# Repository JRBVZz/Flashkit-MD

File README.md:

#### Flashkit MD дампер картриджей для Sega Mega Drive

Данный дампер/программатор позволяет читать и перезаписывать [совместимые картриджи](https://github.com/JRBVZz/SEGA-MD-Cart). Главное отличие данного форка - это возможность использовать адаптеры для флэш памяти в корпусах TSOP48, таким образом можно выпаять память из несовместимого картриджа и перезаписать её. При этом swap byte для записываемого ROM делать не нужно!

**Схема**  
[Schematic PDF](Flashkit-Pics/Flashkit-Schematic.pdf)

**Интерактивный BOM**  
[BoM](BOM/Flashkit-iBOM.html) (для корректного просмотра нужно скачать raw файл)

**Прошивка**  
В папке Flashkit-Firmware находятся исходники проекта для Quartus, логика не менялась, был изменен порядок выводов EPM240.

**Софт**  
В папке Flashkit-Soft находится программа для работы с Flashkit и её исходники. Продвинутую версию программы от MiGeRA можно [скачать здесь](https://github.com/MiGeRA/FlashKit-MD-Plus).

**Использование адаптеров**  
В продаже можно найти дешевые TSOP56 адаптеры под пайку (A) и TSOP48 адаптер для TL866 (B), нужна только верхняя часть с кроваткой для микросхемы. Учтите, что у дампера для разных адаптеров свое посадочное место. Для того, чтобы программа увидела адаптер с установленной памятью, необходимо соединить перемычку "FLASH" на плате дампера.

При запайке чипа памяти в адаптер TSOP56, выводы микросхемы должны располагаться посередине посадочной площадки, т.е. сверху и снизу должно быть свободно по 2 контактные площадки.

Спасибо [**Krikzz**](https://github.com/krikzz) за этот отличный дампер.  
Проект создан в [**KiCad 9**](https://www.kicad.org/).  
PS Герберы не выкладываю специально - это мой небольшой вклад в популяризацию KiCad :smile:

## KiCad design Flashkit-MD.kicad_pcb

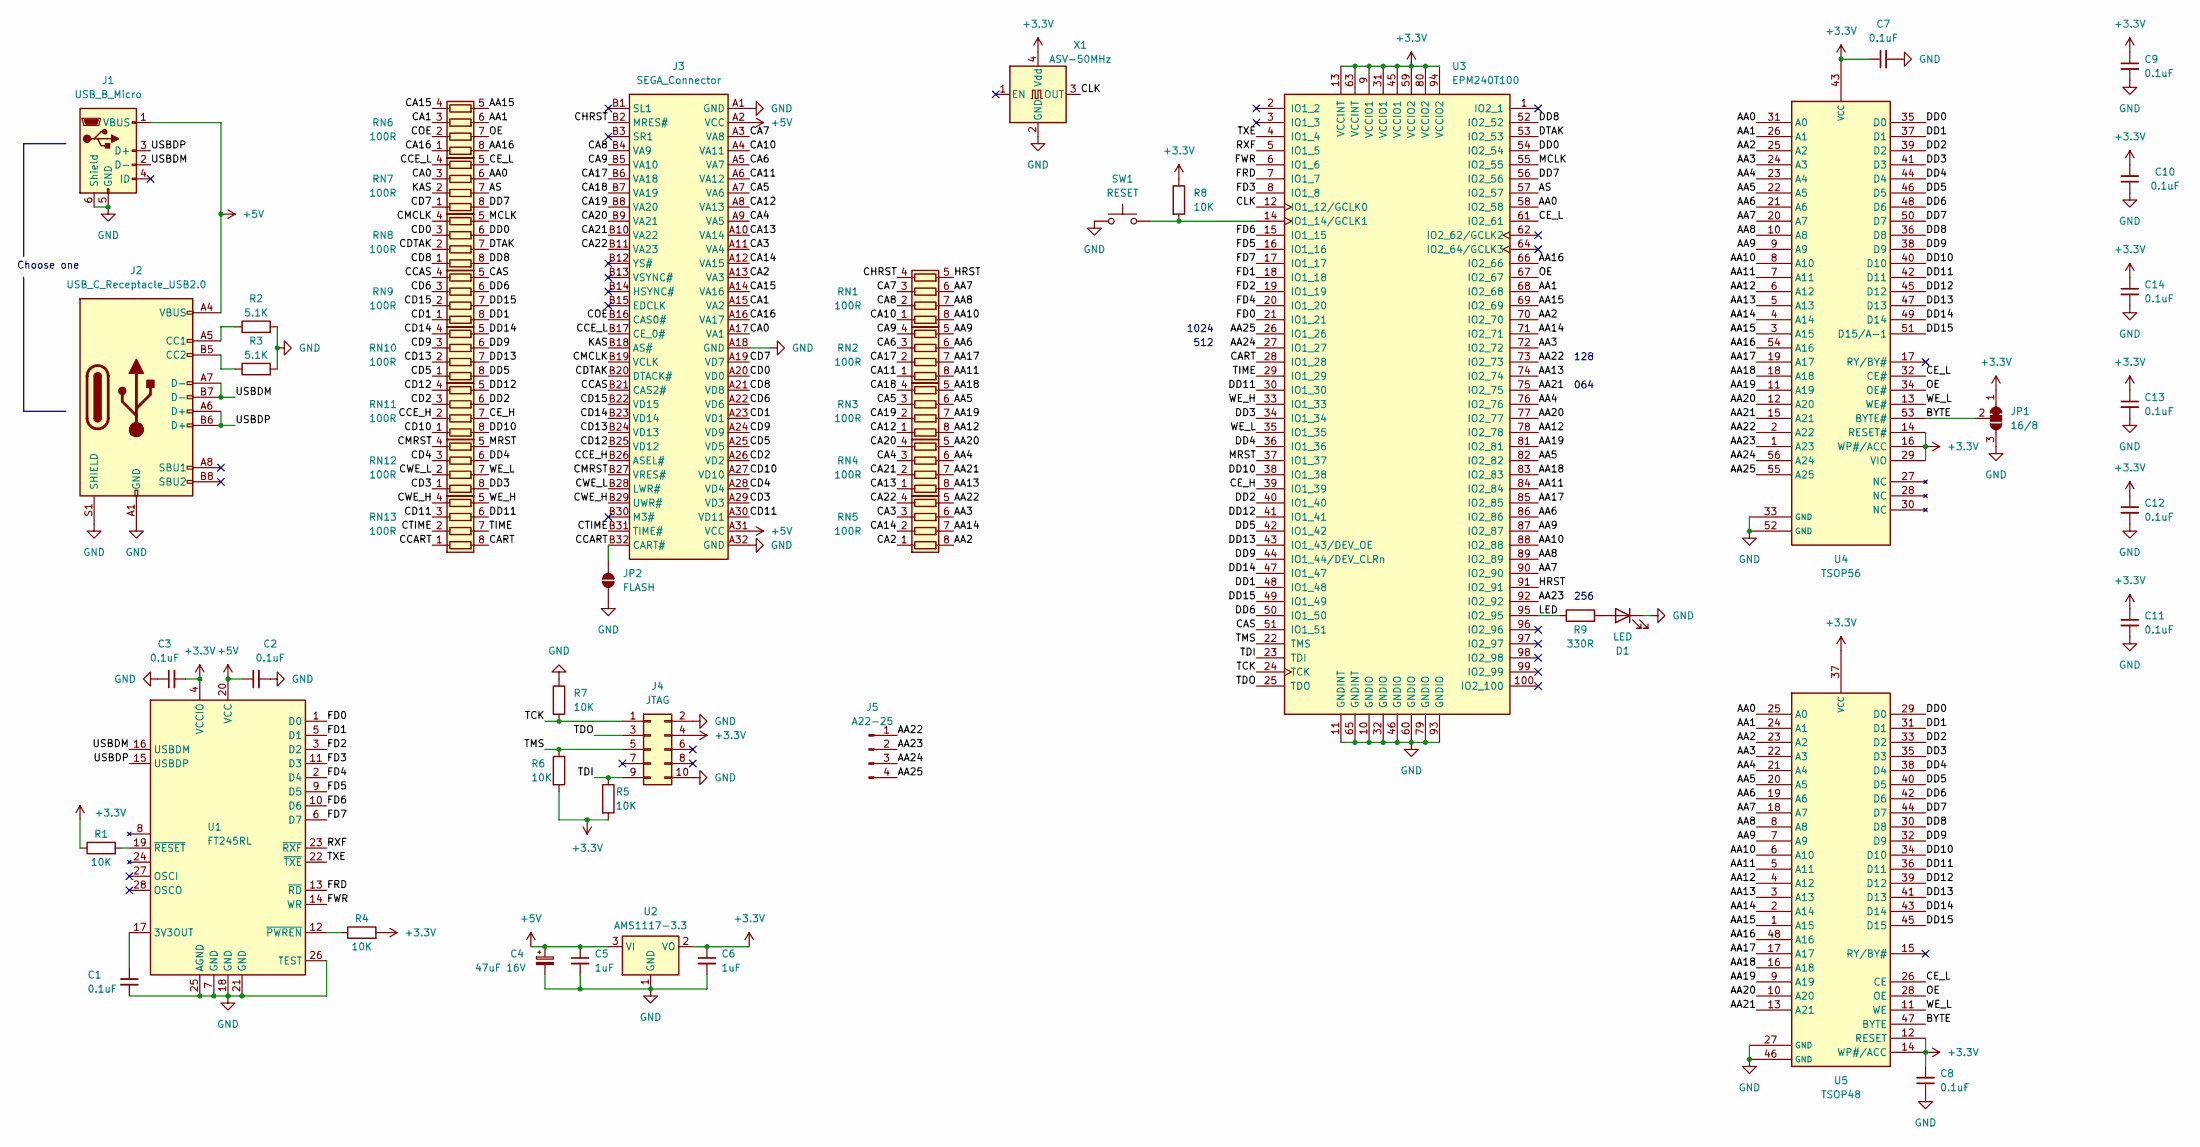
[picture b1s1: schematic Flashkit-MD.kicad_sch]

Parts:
C1, C2, C3, C7, C8, C9, C10, C11, C12, C13, C14: 0.1uF; C_0603_1608Metric
C4: 47uF 16V; CP_Radial_D5.0mm_P2.00mm
C5, C6: 1uF; C_0805_2012Metric
D1: LED; LED_0805_2012Metric
J1: USB_B_Micro; USB_Micro-B_Wuerth_629105150521
J2: USB_C_Receptacle_USB2.0; USB_C_Receptacle_Palconn_UTC16-G
J3: SEGA_Connector; SEGA_Slot
J4: JTAG; PinHeader_2x05_P2.54mm_Vertical
J5: A22-25; PinHeader_1x04_P2.54mm_Vertical
JP1: 16/8; SolderJumper-3_P1.3mm_Bridged12_RoundedPad1.0x1.5mm
JP2: FLASH; SolderJumper-2_P1.3mm_Open_RoundedPad1.0x1.5mm
R1, R4, R5, R6, R7, R8: 10K; R_0805_2012Metric
R2, R3: 5.1K; R_0805_2012Metric
R9: 330R; R_0805_2012Metric
RN1, RN2, RN3, RN4, RN5, RN6, RN7, RN8, RN9, RN10, RN11, RN12, RN13: 100R; R_Array_Convex_4x0603
SW1: RESET; SW_PUSH_6mm
U1: FT245RL; SSOP-28_5.3x10.2mm_P0.65mm
U2: AMS1117-3.3; SOT-223-3_TabPin2
U3: EPM240T100; LQFP-100_14x14mm_P0.5mm
U4: TSOP56; TSOP56-DIP_P2.54mm
U5: TSOP48; TSOP48_DIP_P2.54mm
X1: ASV-50MHz; Oscillator_SMD_Abracon_ASV-4Pin_7.0x5.1mm

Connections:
+3.3V: C3.2, C6.1, C7.1, C8.2, C9.1, C10.2, C11.1, C12.1, C13.1, C14.1, J4.4, JP1.1 (A), R1.1, R4.2, R5.2, R6.2, R8.1, U1.4 (VCCIO), U2.2 (VO), U3.9 (VCCIO1), U3.13 (VCCINT), U3.31 (VCCIO1), U3.45 (VCCIO1), U3.59 (VCCIO2), U3.63 (VCCINT), U3.80 (VCCIO2), U3.94 (VCCIO2), U4.14 (RESET#), U4.16 (WP#/ACC), U4.29 (VIO), U4.43 (VCC), U5.12 (RESET), U5.14 (WP#/ACC), U5.37 (VCC), X1.4 (Vdd)
+5V: C2.1, C4.1, C5.1, J1.1 (VBUS), J2.A4 (VBUS), J2.A9 (VBUS), J2.B4 (VBUS), J2.B9 (VBUS), J3.A2 (VCC), J3.A31 (VCC), U1.20 (VCC), U2.3 (VI)
/AA0: RN7.6 (R3.2), U3.58 (IO2_58), U4.31 (A0), U5.25 (A0)
/AA1: RN6.6 (R3.2), U3.68 (IO2_68), U4.26 (A1), U5.24 (A1)
/AA2: RN5.8 (R1.2), U3.70 (IO2_70), U4.25 (A2), U5.23 (A2)
/AA3: RN5.6 (R3.2), U3.72 (IO2_72), U4.24 (A3), U5.22 (A3)
/AA4: RN4.6 (R3.2), U3.76 (IO2_76), U4.23 (A4), U5.21 (A4)
/AA5: RN3.6 (R3.2), U3.82 (IO2_82), U4.22 (A5), U5.20 (A5)
/AA6: RN2.6 (R3.2), U3.86 (IO2_86), U4.21 (A6), U5.19 (A6)
/AA7: RN1.6 (R3.2), U3.90 (IO2_90), U4.20 (A7), U5.18 (A7)
/AA8: RN1.7 (R2.2), U3.89 (IO2_89), U4.10 (A8), U5.8 (A8)
/AA9: RN2.5 (R4.2), U3.87 (IO2_87), U4.9 (A9), U5.7 (A9)
/AA10: RN1.8 (R1.2), U3.88 (IO2_88), U4.8 (A10), U5.6 (A10)
/AA11: RN2.8 (R1.2), U3.84 (IO2_84), U4.7 (A11), U5.5 (A11)
/AA12: RN3.8 (R1.2), U3.78 (IO2_78), U4.6 (A12), U5.4 (A12)
/AA13: RN4.8 (R1.2), U3.74 (IO2_74), U4.5 (A13), U5.3 (A13)
/AA14: RN5.7 (R2.2), U3.71 (IO2_71), U4.4 (A14), U5.2 (A14)
/AA15: RN6.5 (R4.2), U3.69 (IO2_69), U4.3 (A15), U5.1 (A15)
/AA16: RN6.8 (R1.2), U3.66 (IO2_66), U4.54 (A16), U5.48 (A16)
/AA17: RN2.7 (R2.2), U3.85 (IO2_85), U4.19 (A17), U5.17 (A17)
/AA18: RN3.5 (R4.2), U3.83 (IO2_83), U4.18 (A18), U5.16 (A18)
/AA19: RN3.7 (R2.2), U3.81 (IO2_81), U4.11 (A19), U5.9 (A19)
/AA20: RN4.5 (R4.2), U3.77 (IO2_77), U4.12 (A20), U5.10 (A20)
/AA21: RN4.7 (R2.2), U3.75 (IO2_75), U4.15 (A21), U5.13 (A21)
/AA22: J5.1, RN5.5 (R4.2), U3.73 (IO2_73), U4.2 (A22)
/AA23: J5.2, U3.92 (IO2_92), U4.1 (A23)
/AA24: J5.3, U3.27 (IO1_27), U4.56 (A24)
/AA25: J5.4, U3.26 (IO1_26), U4.55 (A25)
/AS: RN7.7 (R2.2), U3.57 (IO2_57)
/BYTE: JP1.2 (C), U4.53 (BYTE#), U5.47 (BYTE)
/CA0: J3.A17 (VA1), RN7.3 (R3.1)
/CA1: J3.A15 (VA2), RN6.3 (R3.1)
/CA2: J3.A13 (VA3), RN5.1 (R1.1)
/CA3: J3.A11 (VA4), RN5.3 (R3.1)
/CA4: J3.A9 (VA5), RN4.3 (R3.1)
/CA5: J3.A7 (VA6), RN3.3 (R3.1)
/CA6: J3.A5 (VA7), RN2.3 (R3.1)
/CA7: J3.A3 (VA8), RN1.3 (R3.1)
/CA8: J3.B4 (VA9), RN1.2 (R2.1)
/CA9: J3.B5 (VA10), RN2.4 (R4.1)
/CA10: J3.A4 (VA11), RN1.1 (R1.1)
/CA11: J3.A6 (VA12), RN2.1 (R1.1)
/CA12: J3.A8 (VA13), RN3.1 (R1.1)
/CA13: J3.A10 (VA14), RN4.1 (R1.1)
/CA14: J3.A12 (VA15), RN5.2 (R2.1)
/CA15: J3.A14 (VA16), RN6.4 (R4.1)
/CA16: J3.A16 (VA17), RN6.1 (R1.1)
/CA17: J3.B6 (VA18), RN2.2 (R2.1)
/CA18: J3.B7 (VA19), RN3.4 (R4.1)
/CA19: J3.B8 (VA20), RN3.2 (R2.1)
/CA20: J3.B9 (VA21), RN4.4 (R4.1)
/CA21: J3.B10 (VA22), RN4.2 (R2.1)
/CA22: J3.B11 (VA23), RN5.4 (R4.1)
/CART: RN13.8 (R1.2), U3.28 (IO1_28)
/CAS: RN9.5 (R4.2), U3.51 (IO1_51)
/CCART: J3.B32 (CART#), JP2.2 (B), RN13.1 (R1.1)
/CCAS: J3.B21 (CAS2#), RN9.4 (R4.1)
/CCE_H: J3.B26 (ASEL#), RN11.2 (R2.1)
/CCE_L: J3.B17 (CE_0#), RN7.4 (R4.1)
/CD0: J3.A20 (VD0), RN8.3 (R3.1)
/CD1: J3.A23 (VD1), RN9.1 (R1.1)
/CD2: J3.A26 (VD2), RN11.3 (R3.1)
/CD3: J3.A29 (VD3), RN12.1 (R1.1)
/CD4: J3.A28 (VD4), RN12.3 (R3.1)
/CD5: J3.A25 (VD5), RN10.1 (R1.1)
/CD6: J3.A22 (VD6), RN9.3 (R3.1)
/CD7: J3.A19 (VD7), RN7.1 (R1.1)
/CD8: J3.A21 (VD8), RN8.1 (R1.1)
/CD9: J3.A24 (VD9), RN10.3 (R3.1)
/CD10: J3.A27 (VD10), RN11.1 (R1.1)
/CD11: J3.A30 (VD11), RN13.3 (R3.1)
/CD12: J3.B25 (VD12), RN11.4 (R4.1)
/CD13: J3.B24 (VD13), RN10.2 (R2.1)
/CD14: J3.B23 (VD14), RN10.4 (R4.1)
/CD15: J3.B22 (VD15), RN9.2 (R2.1)
/CDTAK: J3.B20 (DTACK#), RN8.2 (R2.1)
/CE_H: RN11.7 (R2.2), U3.39 (IO1_39)
/CE_L: RN7.5 (R4.2), U3.61 (IO2_61), U4.32 (CE#), U5.26 (CE)
/CHRST: J3.B2 (MRES#), RN1.4 (R4.1)
/CLK: U3.12 (IO1_12/GCLK0), X1.3 (OUT)
/CMCLK: J3.B19 (VCLK), RN8.4 (R4.1)
/CMRST: J3.B27 (VRES#), RN12.4 (R4.1)
/COE: J3.B16 (CAS0#), RN6.2 (R2.1)
/CTIME: J3.B31 (TIME#), RN13.2 (R2.1)
/CWE_H: J3.B29 (UWR#), RN13.4 (R4.1)
/CWE_L: J3.B28 (LWR#), RN12.2 (R2.1)
/DD0: RN8.6 (R3.2), U3.54 (IO2_54), U4.35 (D0), U5.29 (D0)
/DD1: RN9.8 (R1.2), U3.48 (IO1_48), U4.37 (D1), U5.31 (D1)
/DD2: RN11.6 (R3.2), U3.40 (IO1_40), U4.39 (D2), U5.33 (D2)
/DD3: RN12.8 (R1.2), U3.34 (IO1_34), U4.41 (D3), U5.35 (D3)
/DD4: RN12.6 (R3.2), U3.36 (IO1_36), U4.44 (D4), U5.38 (D4)
/DD5: RN10.8 (R1.2), U3.42 (IO1_42), U4.46 (D5), U5.40 (D5)
/DD6: RN9.6 (R3.2), U3.50 (IO1_50), U4.48 (D6), U5.42 (D6)
/DD7: RN7.8 (R1.2), U3.56 (IO2_56), U4.50 (D7), U5.44 (D7)
/DD8: RN8.8 (R1.2), U3.52 (IO2_52), U4.36 (D8), U5.30 (D8)
/DD9: RN10.6 (R3.2), U3.44 (IO1_44/DEV_CLRn), U4.38 (D9), U5.32 (D9)
/DD10: RN11.8 (R1.2), U3.38 (IO1_38), U4.40 (D10), U5.34 (D10)
/DD11: RN13.6 (R3.2), U3.30 (IO1_30), U4.42 (D11), U5.36 (D11)
/DD12: RN11.5 (R4.2), U3.41 (IO1_41), U4.45 (D12), U5.39 (D12)
/DD13: RN10.7 (R2.2), U3.43 (IO1_43/DEV_OE), U4.47 (D13), U5.41 (D13)
/DD14: RN10.5 (R4.2), U3.47 (IO1_47), U4.49 (D14), U5.43 (D14)
/DD15: RN9.7 (R2.2), U3.49 (IO1_49), U4.51 (D15/A-1), U5.45 (D15)
/DTAK: RN8.7 (R2.2), U3.53 (IO2_53)
/FD0: U1.1 (D0), U3.21 (IO1_21)
/FD1: U1.5 (D1), U3.18 (IO1_18)
/FD2: U1.3 (D2), U3.19 (IO1_19)
/FD3: U1.11 (D3), U3.8 (IO1_8)
/FD4: U1.2 (D4), U3.20 (IO1_20)
/FD5: U1.9 (D5), U3.16 (IO1_16)
/FD6: U1.10 (D6), U3.15 (IO1_15)
/FD7: U1.6 (D7), U3.17 (IO1_17)
/FRD: U1.13 (~RD), U3.7 (IO1_7)
/FWR: U1.14 (WR), U3.6 (IO1_6)
/HRST: RN1.5 (R4.2), U3.91 (IO2_91)
/KAS: J3.B18 (AS#), RN7.2 (R2.1)
/LED: R9.1, U3.95 (IO2_95)
/MCLK: RN8.5 (R4.2), U3.55 (IO2_55)
/MRST: RN12.5 (R4.2), U3.37 (IO1_37)
/OE: RN6.7 (R2.2), U3.67 (IO2_67), U4.34 (OE#), U5.28 (OE)
/RXF: U1.23 (~RXF), U3.5 (IO1_5)
/TCK: J4.1, R7.2, U3.24 (TCK)
/TDI: J4.9, R5.1, U3.23 (TDI)
/TDO: J4.3, U3.25 (TDO)
/TIME: RN13.7 (R2.2), U3.29 (IO1_29)
/TMS: J4.5, R6.1, U3.22 (TMS)
/TXE: U1.22 (~TXE), U3.4 (IO1_4)
/USBDM: J1.2 (D-), J2.A7 (D-), J2.B7 (D-), U1.16 (USBDM)
/USBDP: J1.3 (D+), J2.A6 (D+), J2.B6 (D+), U1.15 (USBDP)
/WE_H: RN13.5 (R4.2), U3.33 (IO1_33)
/WE_L: RN12.7 (R2.2), U3.35 (IO1_35), U4.13 (WE#), U5.11 (WE)
GND: C1.2, C2.2, C3.1, C4.2, C5.2, C6.2, C7.2, C8.1, C9.2, C10.1, C11.2, C12.2, C13.2, C14.2, D1.1 (K), J1.5 (GND), J1.6 (Shield), J2.A1 (GND), J2.A12 (GND), J2.B1 (GND), J2.B12 (GND), J2.S1 (SHIELD), J3.A1 (GND), J3.A18 (GND), J3.A32 (GND), J4.2, J4.10, JP1.3 (B), JP2.1 (A), R2.2, R3.2, R7.1, SW1.1, U1.7 (GND), U1.18 (GND), U1.21 (GND), U1.25 (AGND), U1.26 (TEST), U2.1 (GND), U3.10 (GNDIO), U3.11 (GNDINT), U3.32 (GNDIO), U3.46 (GNDIO), U3.60 (GNDIO), U3.65 (GNDINT), U3.79 (GNDIO), U3.93 (GNDIO), U4.33 (GND), U4.52 (GND), U5.27 (GND), U5.46 (GND), X1.2 (GND)
unnamed: D1.2 (A), R9.2
unnamed: J2.A5 (CC1), R2.1
unnamed: J2.B5 (CC2), R3.1
unnamed: C1.1, U1.17 (3V3OUT)
unnamed: R4.1, U1.12 (~PWREN)
unnamed: R1.2, U1.19 (~RESET)
unnamed: R8.2, SW1.2, U3.14 (IO1_14/GCLK1)

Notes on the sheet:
512
1024
128
064
256
Choose one

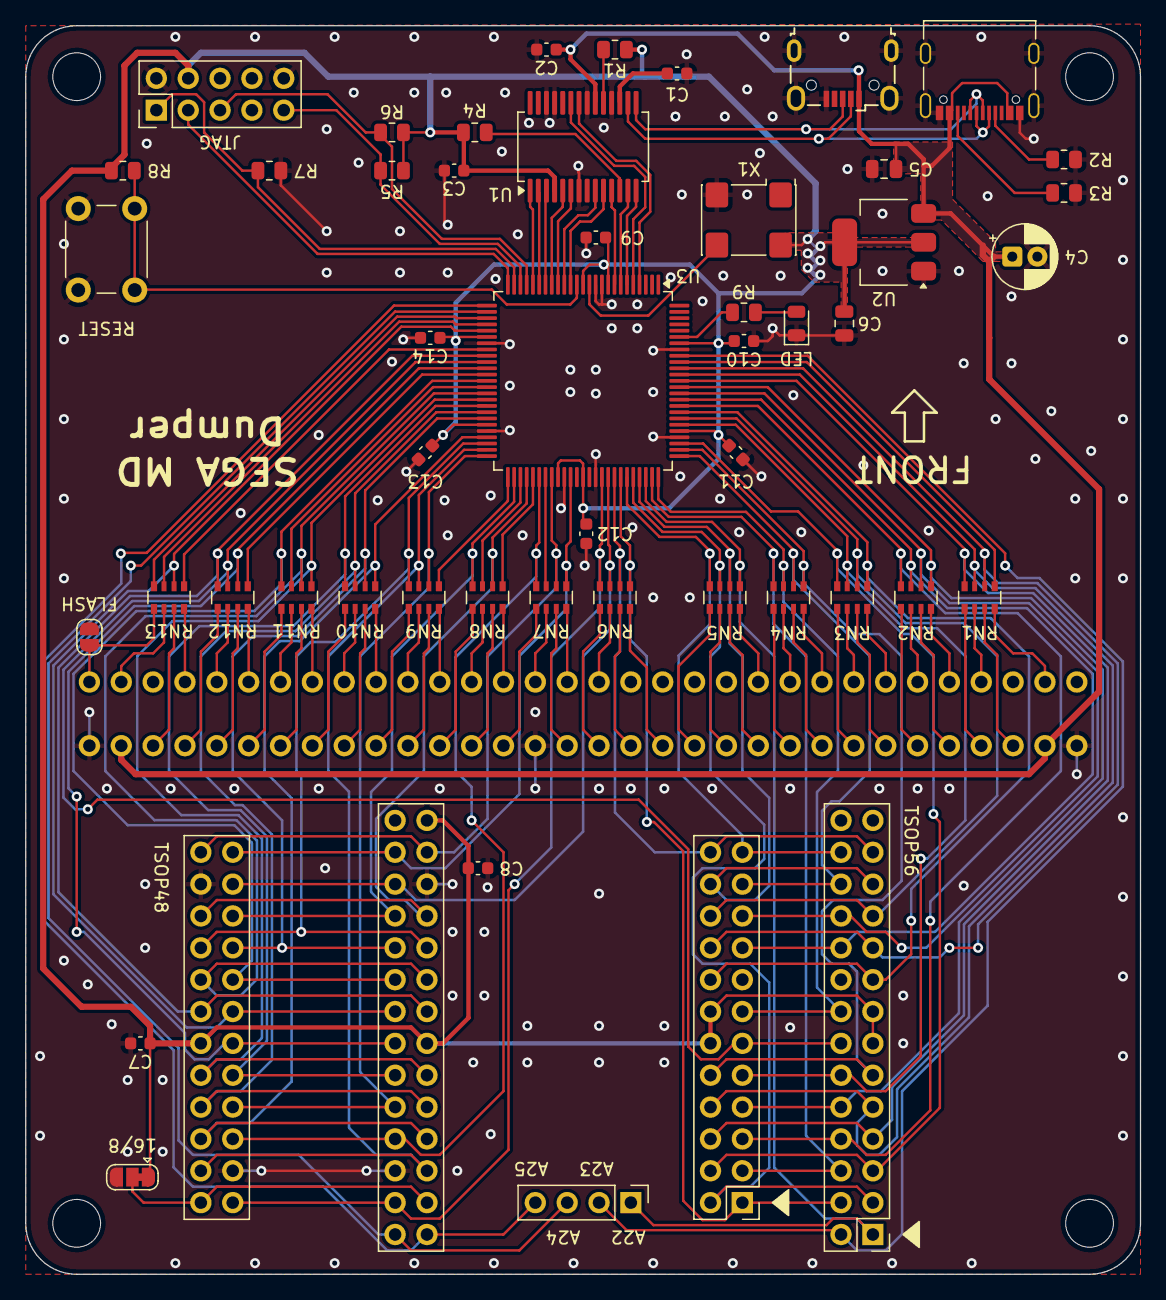
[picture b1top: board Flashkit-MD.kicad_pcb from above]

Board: 2 copper layers, 88.9 x 99.6 mm, 51 parts (0 on the bottom side), 138 nets.

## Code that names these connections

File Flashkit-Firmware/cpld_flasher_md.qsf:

# -------------------------------------------------------------------------- #
#
# Copyright (C) 1991-2013 Altera Corporation
# Your use of Altera Corporation's design tools, logic functions 
# and other software and tools, and its AMPP partner logic 
# functions, and any output files from any of the foregoing 
# (including device programming or simulation files), and any 
# associated documentation or information are expressly subject 
# to the terms and conditions of the Altera Program License 
# Subscription Agreement, Altera MegaCore Function License 
# Agreement, or other applicable license agreement, including, 
# without limitation, that your use is for the sole purpose of 
# programming logic devices manufactured by Altera and sold by 
# Altera or its authorized distributors.  Please refer to the 
# applicable agreement for further details.
#
# -------------------------------------------------------------------------- #
#
# Quartus II 64-Bit
# Version 13.0.1 Build 232 06/12/2013 Service Pack 1 SJ Web Edition
# Date created = 08:10:07  December 13, 2013
#
# -------------------------------------------------------------------------- #
#
# Notes:
#
# 1) The default values for assignments are stored in the file:
#		cpld_flasher_md_assignment_defaults.qdf
#    If this file doesn't exist, see file:
#		assignment_defaults.qdf
#
# 2) Altera recommends that you do not modify this file. This
#    file is updated automatically by the Quartus II software
#    and any changes you make may be lost or overwritten.
#
# -------------------------------------------------------------------------- #


set_global_assignment -name FAMILY "MAX II"
set_global_assignment -name DEVICE EPM240T100C5
set_global_assignment -name TOP_LEVEL_ENTITY flasher_md
set_global_assignment -name ORIGINAL_QUARTUS_VERSION "13.0 SP1"
set_global_assignment -name PROJECT_CREATION_TIME_DATE "08:10:07  DECEMBER 13, 2013"
set_global_assignment -name LAST_QUARTUS_VERSION "18.0.0 Standard Edition"
set_global_assignment -name PROJECT_OUTPUT_DIRECTORY output_files
set_global_assignment -name MIN_CORE_JUNCTION_TEMP 0
set_global_assignment -name MAX_CORE_JUNCTION_TEMP 85
set_global_assignment -name DEVICE_FILTER_PACKAGE "ANY QFP"
set_global_assignment -name DEVICE_FILTER_PIN_COUNT 100
set_global_assignment -name ERROR_CHECK_FREQUENCY_DIVISOR "-1"
set_global_assignment -name POWER_EXT_SUPPLY_VOLTAGE_TO_REGULATOR 3.3V
set_global_assignment -name VERILOG_FILE flasher_md.v
set_global_assignment -name STRATIX_DEVICE_IO_STANDARD "3.3-V LVTTL"
set_location_assignment PIN_58 -to addr[0]
set_location_assignment PIN_68 -to addr[1]
set_location_assignment PIN_70 -to addr[2]
set_location_assignment PIN_72 -to addr[3]
set_location_assignment PIN_76 -to addr[4]
set_location_assignment PIN_82 -to addr[5]
set_location_assignment PIN_86 -to addr[6]
set_location_assignment PIN_90 -to addr[7]
set_location_assignment PIN_89 -to addr[8]
set_location_assignment PIN_87 -to addr[9]
set_location_assignment PIN_88 -to addr[10]
set_location_assignment PIN_84 -to addr[11]
set_location_assignment PIN_78 -to addr[12]
set_location_assignment PIN_74 -to addr[13]
set_location_assignment PIN_71 -to addr[14]
set_location_assignment PIN_69 -to addr[15]
set_location_assignment PIN_66 -to addr[16]
set_location_assignment PIN_85 -to addr[17]
set_location_assignment PIN_83 -to addr[18]
set_location_assignment PIN_81 -to addr[19]
set_location_assignment PIN_77 -to addr[20]
set_location_assignment PIN_75 -to addr[21]
set_location_assignment PIN_73 -to addr[22]
set_location_assignment PIN_57 -to as
set_location_assignment PIN_28 -to cart
set_location_assignment PIN_51 -to cas
set_location_assignment PIN_39 -to ce_hi
set_location_assignment PIN_61 -to ce_lo
set_location_assignment PIN_12 -to clk
set_location_assignment PIN_54 -to dat[0]
set_location_assignment PIN_48 -to dat[1]
set_location_assignment PIN_40 -to dat[2]
set_location_assignment PIN_34 -to dat[3]
set_location_assignment PIN_36 -to dat[4]
set_location_assignment PIN_42 -to dat[5]
set_location_assignment PIN_50 -to dat[6]
set_location_assignment PIN_56 -to dat[7]
set_location_assignment PIN_52 -to dat[8]
set_location_assignment PIN_44 -to dat[9]
set_location_assignment PIN_38 -to dat[10]
set_location_assignment PIN_30 -to dat[11]
set_location_assignment PIN_41 -to dat[12]
set_location_assignment PIN_43 -to dat[13]
set_location_assignment PIN_47 -to dat[14]
set_location_assignment PIN_49 -to dat[15]
set_location_assignment PIN_53 -to dtak
set_location_assignment PIN_21 -to fdat[0]
set_location_assignment PIN_18 -to fdat[1]
set_location_assignment PIN_19 -to fdat[2]
set_location_assignment PIN_8 -to fdat[3]
set_location_assignment PIN_20 -to fdat[4]
set_location_assignment PIN_16 -to fdat[5]
set_location_assignment PIN_15 -to fdat[6]
set_location_assignment PIN_17 -to fdat[7]
set_location_assignment PIN_7 -to frd
set_location_assignment PIN_6 -to fwr
set_location_assignment PIN_91 -to hrst
set_location_assignment PIN_95 -to led
set_location_assignment PIN_55 -to mclk
set_location_assignment PIN_37 -to mrst
set_location_assignment PIN_67 -to oe
set_location_assignment PIN_14 -to rst
set_location_assignment PIN_5 -to rxf
set_location_assignment PIN_29 -to tim
set_location_assignment PIN_4 -to txe
set_location_assignment PIN_33 -to we_hi
set_location_assignment PIN_35 -to we_lo
set_instance_assignment -name WEAK_PULL_UP_RESISTOR ON -to dat[15]
set_instance_assignment -name WEAK_PULL_UP_RESISTOR ON -to dat[14]
set_instance_assignment -name WEAK_PULL_UP_RESISTOR ON -to dat[13]
set_instance_assignment -name WEAK_PULL_UP_RESISTOR ON -to dat[12]
set_instance_assignment -name WEAK_PULL_UP_RESISTOR ON -to dat[11]
set_instance_assignment -name WEAK_PULL_UP_RESISTOR ON -to dat[10]
set_instance_assignment -name WEAK_PULL_UP_RESISTOR ON -to dat[9]
set_instance_assignment -name WEAK_PULL_UP_RESISTOR ON -to dat[8]
set_instance_assignment -name WEAK_PULL_UP_RESISTOR ON -to dat[7]
set_instance_assignment -name WEAK_PULL_UP_RESISTOR ON -to dat[6]
set_instance_assignment -name WEAK_PULL_UP_RESISTOR ON -to dat[5]
set_instance_assignment -name WEAK_PULL_UP_RESISTOR ON -to dat[4]
set_instance_assignment -name WEAK_PULL_UP_RESISTOR ON -to dat[3]
set_instance_assignment -name WEAK_PULL_UP_RESISTOR ON -to dat[2]
set_instance_assignment -name WEAK_PULL_UP_RESISTOR ON -to dat[1]
set_instance_assignment -name WEAK_PULL_UP_RESISTOR ON -to dat[0]
set_instance_assignment -name WEAK_PULL_UP_RESISTOR ON -to dtak
set_instance_assignment -name WEAK_PULL_UP_RESISTOR ON -to mrst
set_instance_assignment -name WEAK_PULL_UP_RESISTOR ON -to hrst
set_instance_assignment -name WEAK_PULL_UP_RESISTOR ON -to cart

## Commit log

2025-11-23 Add KiCad Project
2025-11-24 ReadMe update
